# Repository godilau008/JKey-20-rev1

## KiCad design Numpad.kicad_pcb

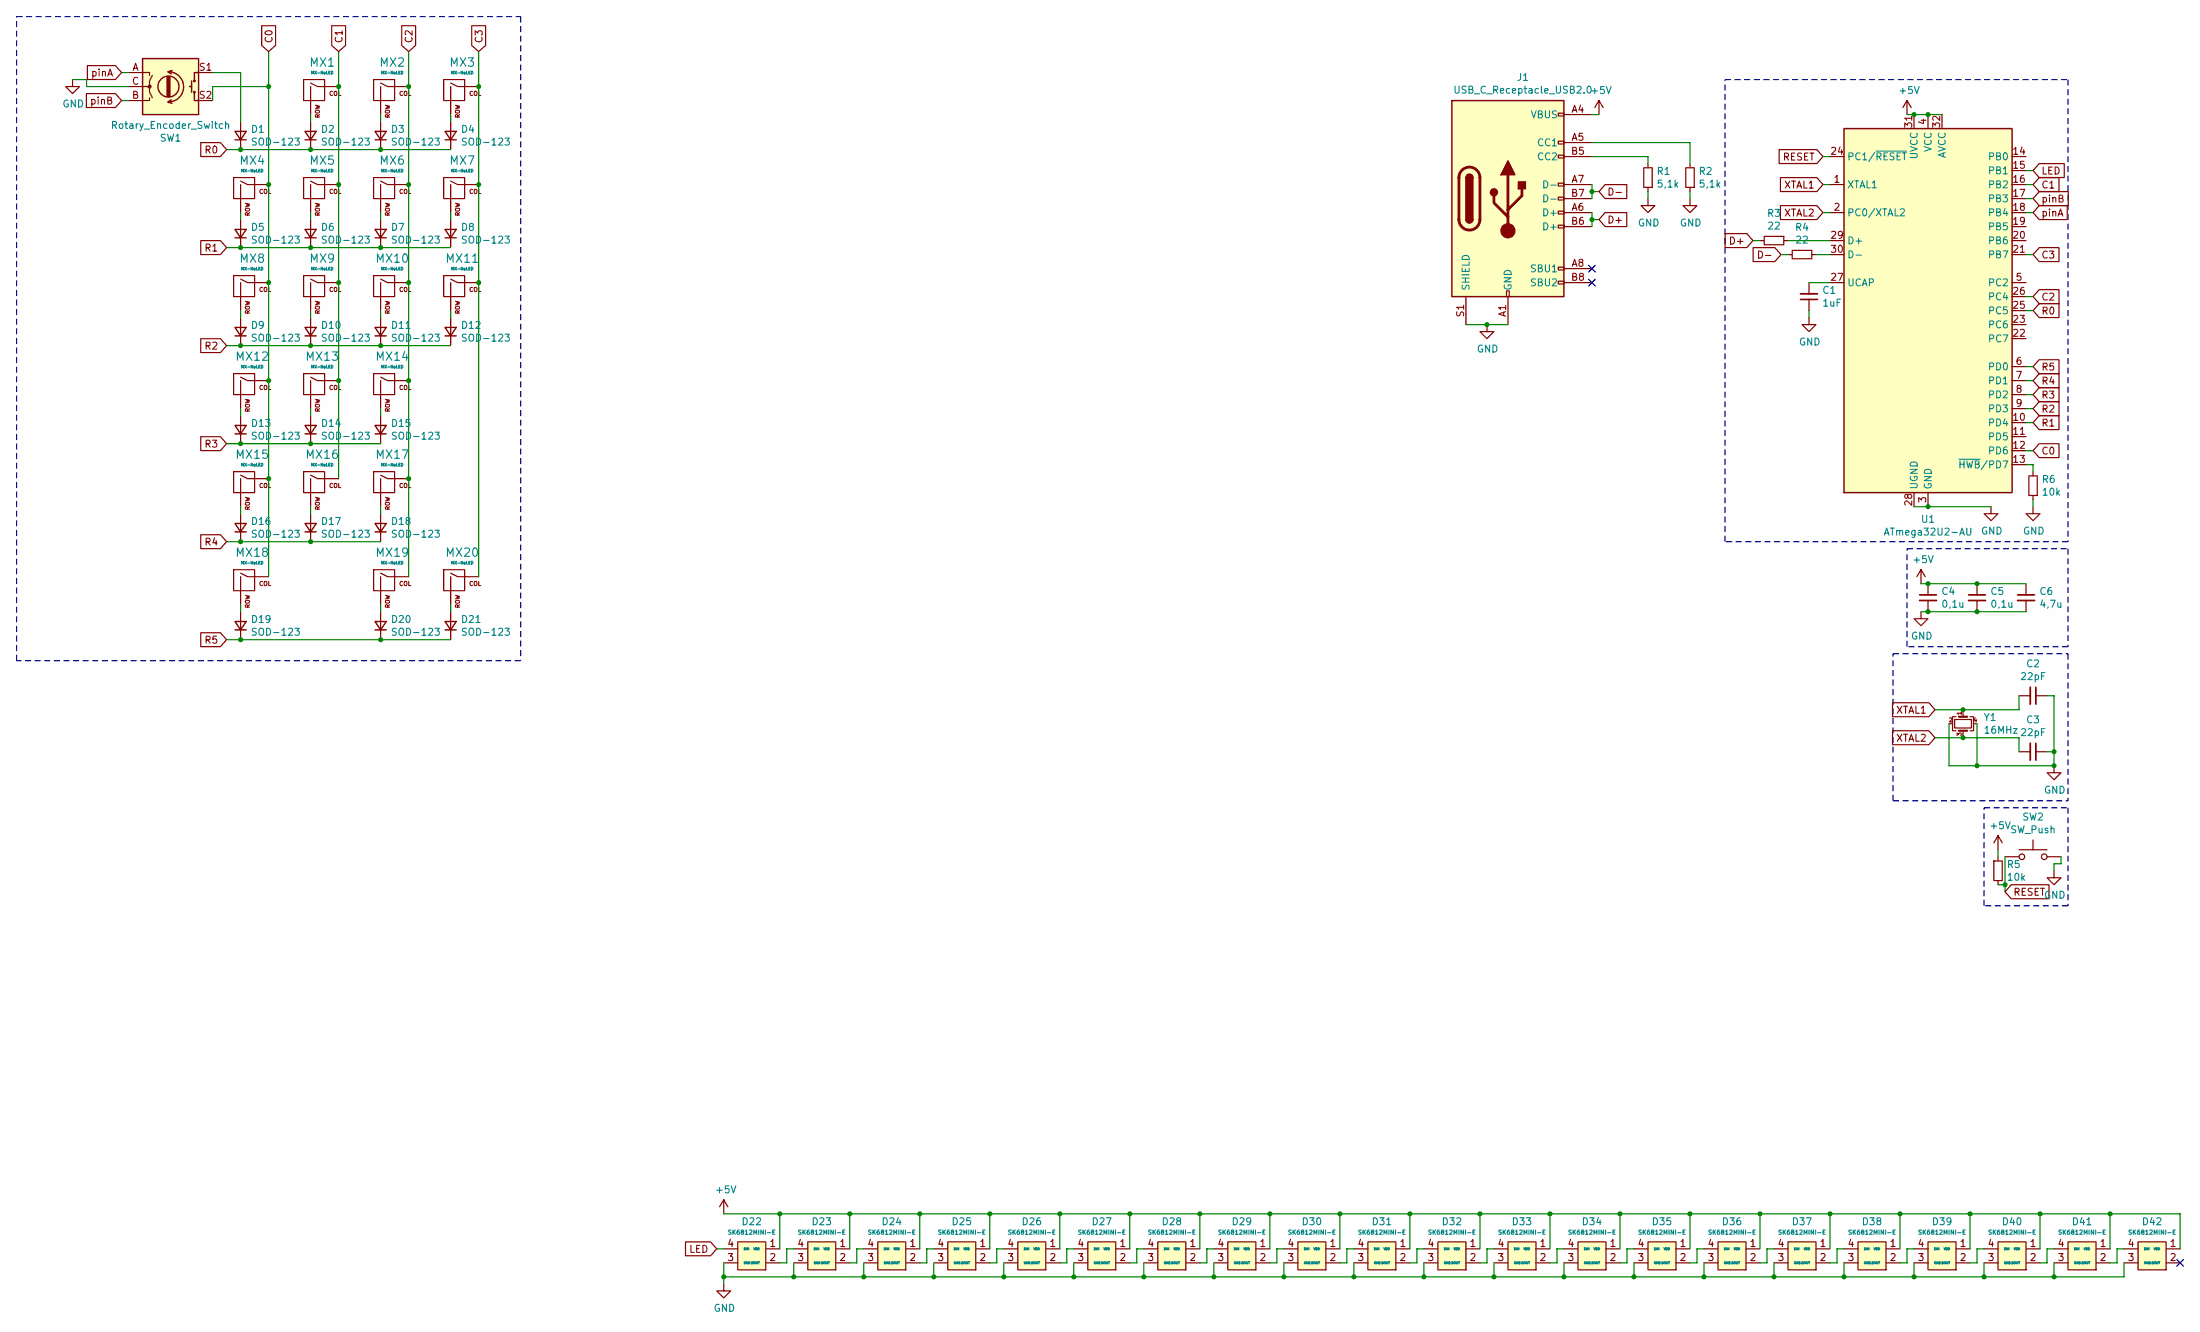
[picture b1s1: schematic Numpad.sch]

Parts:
C1: 1uF; C_0805_2012Metric_Pad1.15x1.40mm_HandSolder
C2, C3: 22pF; C_0805_2012Metric_Pad1.15x1.40mm_HandSolder
C4, C5: 0,1u; C_0805_2012Metric_Pad1.15x1.40mm_HandSolder
C6: 4,7u; C_0805_2012Metric_Pad1.15x1.40mm_HandSolder
D1, D2, D3, D4, D5, D6, D7, D8, D9, D10, D11, D12, D13, D14, D15, D16, D17, D18, D19, D20, D21: SOD-123; D_SOD-123
D22, D23, D24, D25, D26, D27, D28, D29, D30, D31, D32, D33, D34, D35, D36, D37, D38, D39, D40, D41, D42: SK6812MINI-E; LED_SK6812MINI-E_HOLE
J1: USB_C_Receptacle_USB2.0; USB_C_Receptacle_GCT_USB4085
MX1, MX2, MX3, MX4, MX5, MX6, MX7, MX8, MX9, MX10, MX12, MX13, MX14, MX15, MX16, MX17, MX19: MX-NoLED; MXOnly-1U-NoLED
MX11, MX20: MX-NoLED; MXOnly-2U-NoLED-Vertical
MX18: MX-NoLED; MXOnly-2U-NoLED
R1, R2: 5,1k; R_0805_2012Metric_Pad1.15x1.40mm_HandSolder
R3, R4: 22; R_0805_2012Metric_Pad1.15x1.40mm_HandSolder
R5, R6: 10k; R_0805_2012Metric_Pad1.15x1.40mm_HandSolder
SW1: Rotary_Encoder_Switch; RotaryEncoder_Alps_EC11E-Switch_Vertical_H20mm
SW2: SW_Push; SW_SPST_TL3342
U1: ATmega32U2-AU; TQFP-32_7x7mm_P0.8mm
Y1: 16MHz; Crystal_SMD_3225-4Pin_3.2x2.5mm_HandSoldering

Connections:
+5V: C4.1, C5.1, C6.1, D22.1 (VDD), D23.1 (VDD), D24.1 (VDD), D25.1 (VDD), D26.1 (VDD), D27.1 (VDD), D28.1 (VDD), D29.1 (VDD), D30.1 (VDD), D31.1 (VDD), D32.1 (VDD), D33.1 (VDD), D34.1 (VDD), D35.1 (VDD), D36.1 (VDD), D37.1 (VDD), D38.1 (VDD), D39.1 (VDD), D40.1 (VDD), D41.1 (VDD), D42.1 (VDD), J1.A4 (VBUS), J1.A9 (VBUS), J1.B4 (VBUS), J1.B9 (VBUS), R5.1, U1.4 (VCC), U1.31 (UVCC), U1.32 (AVCC)
C0: MX4.1 (COL), MX8.1 (COL), MX12.1 (COL), MX15.1 (COL), MX18.1 (COL), SW1.S2, U1.12 (PD6)
C1: MX1.1 (COL), MX5.1 (COL), MX9.1 (COL), MX13.1 (COL), MX16.1 (COL), U1.16 (PB2)
C2: MX2.1 (COL), MX6.1 (COL), MX10.1 (COL), MX14.1 (COL), MX17.1 (COL), MX19.1 (COL), U1.26 (PC4)
C3: MX3.1 (COL), MX7.1 (COL), MX11.1 (COL), MX20.1 (COL), U1.21 (PB7)
D+: J1.A6 (D+), J1.B6 (D+), R3.2
D-: J1.A7 (D-), J1.B7 (D-), R4.2
GND: C1.1, C2.1, C3.1, C4.2, C5.2, C6.2, D22.3 (GND), D23.3 (GND), D24.3 (GND), D25.3 (GND), D26.3 (GND), D27.3 (GND), D28.3 (GND), D29.3 (GND), D30.3 (GND), D31.3 (GND), D32.3 (GND), D33.3 (GND), D34.3 (GND), D35.3 (GND), D36.3 (GND), D37.3 (GND), D38.3 (GND), D39.3 (GND), D40.3 (GND), D41.3 (GND), D42.3 (GND), J1.A1 (GND), J1.A12 (GND), J1.B1 (GND), J1.B12 (GND), J1.S1 (SHIELD), R1.1, R2.1, R6.1, SW1.C, SW2.2, U1.3 (GND), U1.28 (UGND), Y1.2, Y1.4
LED: D22.4 (DIN), U1.15 (PB1)
unnamed: C1.2, U1.27 (UCAP)
unnamed: D1.2 (A), SW1.S1
unnamed: D2.2 (A), MX1.2 (ROW)
unnamed: D3.2 (A), MX2.2 (ROW)
unnamed: D4.2 (A), MX3.2 (ROW)
unnamed: D5.2 (A), MX4.2 (ROW)
unnamed: D6.2 (A), MX5.2 (ROW)
unnamed: D7.2 (A), MX6.2 (ROW)
unnamed: D8.2 (A), MX7.2 (ROW)
unnamed: D9.2 (A), MX8.2 (ROW)
unnamed: D10.2 (A), MX9.2 (ROW)
unnamed: D11.2 (A), MX10.2 (ROW)
unnamed: D12.2 (A), MX11.2 (ROW)
unnamed: D13.2 (A), MX12.2 (ROW)
unnamed: D14.2 (A), MX13.2 (ROW)
unnamed: D15.2 (A), MX14.2 (ROW)
unnamed: D16.2 (A), MX15.2 (ROW)
unnamed: D17.2 (A), MX16.2 (ROW)
unnamed: D18.2 (A), MX17.2 (ROW)
unnamed: D19.2 (A), MX18.2 (ROW)
unnamed: D20.2 (A), MX19.2 (ROW)
unnamed: D21.2 (A), MX20.2 (ROW)
unnamed: D22.2 (DOUT), D23.4 (DIN)
unnamed: D23.2 (DOUT), D24.4 (DIN)
unnamed: D24.2 (DOUT), D25.4 (DIN)
unnamed: D25.2 (DOUT), D26.4 (DIN)
unnamed: D26.2 (DOUT), D27.4 (DIN)
unnamed: D27.2 (DOUT), D28.4 (DIN)
unnamed: D28.2 (DOUT), D29.4 (DIN)
unnamed: D29.2 (DOUT), D30.4 (DIN)
unnamed: D30.2 (DOUT), D31.4 (DIN)
unnamed: D31.2 (DOUT), D32.4 (DIN)
unnamed: D32.2 (DOUT), D33.4 (DIN)
unnamed: D33.2 (DOUT), D34.4 (DIN)
unnamed: D34.2 (DOUT), D35.4 (DIN)
unnamed: D35.2 (DOUT), D36.4 (DIN)
unnamed: D36.2 (DOUT), D37.4 (DIN)
unnamed: D37.2 (DOUT), D38.4 (DIN)
unnamed: D38.2 (DOUT), D39.4 (DIN)
unnamed: D39.2 (DOUT), D40.4 (DIN)
unnamed: D40.2 (DOUT), D41.4 (DIN)
unnamed: D41.2 (DOUT), D42.4 (DIN)
unnamed: J1.A5 (CC1), R2.2
unnamed: J1.B5 (CC2), R1.2
unnamed: R3.1, U1.29 (D+)
unnamed: R4.1, U1.30 (D-)
unnamed: R6.2, U1.13 (~HWB~/PD7)
R0: D1.1 (K), D2.1 (K), D3.1 (K), D4.1 (K), U1.25 (PC5)
R1: D5.1 (K), D6.1 (K), D7.1 (K), D8.1 (K), U1.10 (PD4)
R2: D9.1 (K), D10.1 (K), D11.1 (K), D12.1 (K), U1.9 (PD3)
R3: D13.1 (K), D14.1 (K), D15.1 (K), U1.8 (PD2)
R4: D16.1 (K), D17.1 (K), D18.1 (K), U1.7 (PD1)
R5: D19.1 (K), D20.1 (K), D21.1 (K), U1.6 (PD0)
RESET: R5.2, SW2.1, U1.24 (PC1/~RESET)
XTAL1: C2.2, U1.1 (XTAL1), Y1.1
XTAL2: C3.2, U1.2 (PC0/XTAL2), Y1.3
pinA: SW1.A, U1.18 (PB4)
pinB: SW1.B, U1.17 (PB3)

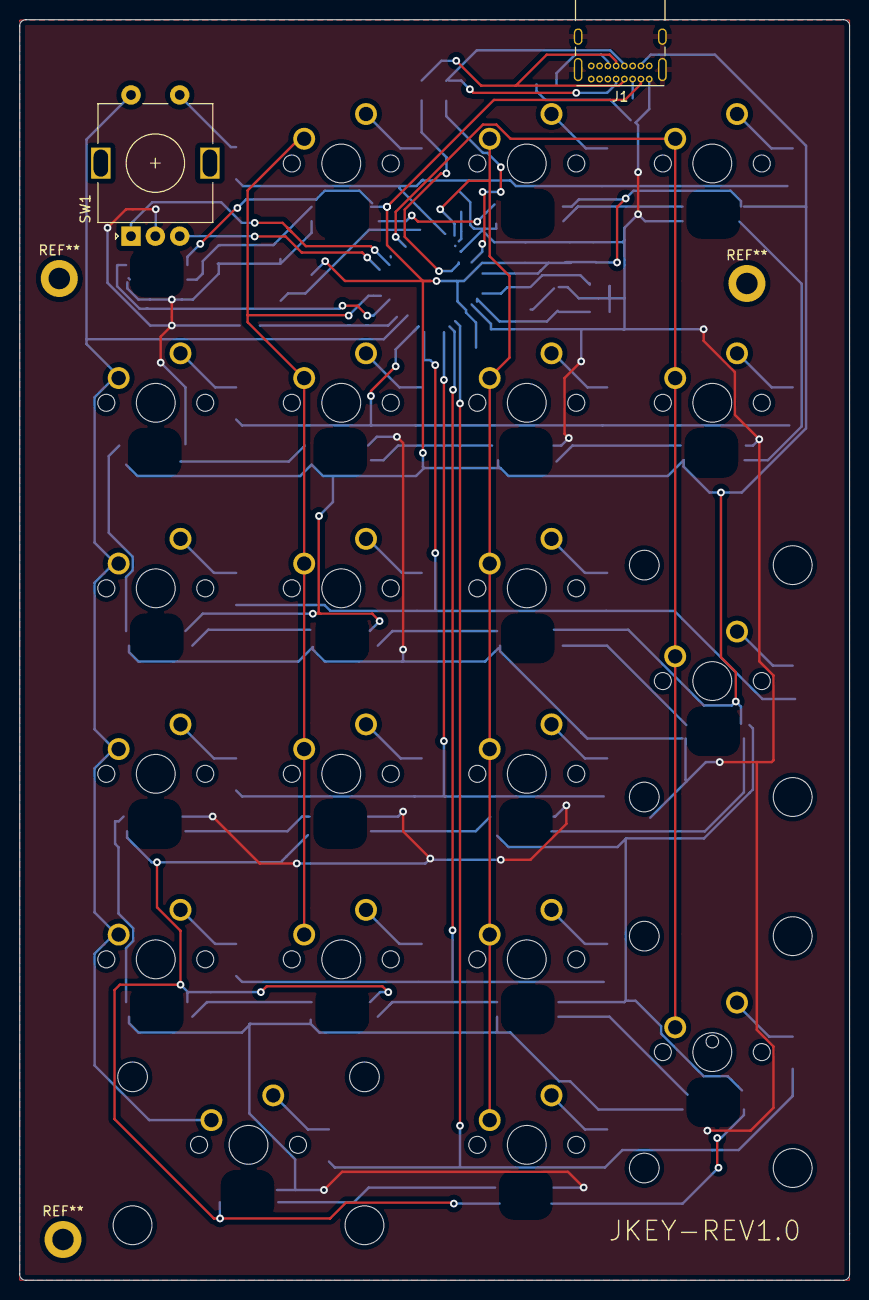
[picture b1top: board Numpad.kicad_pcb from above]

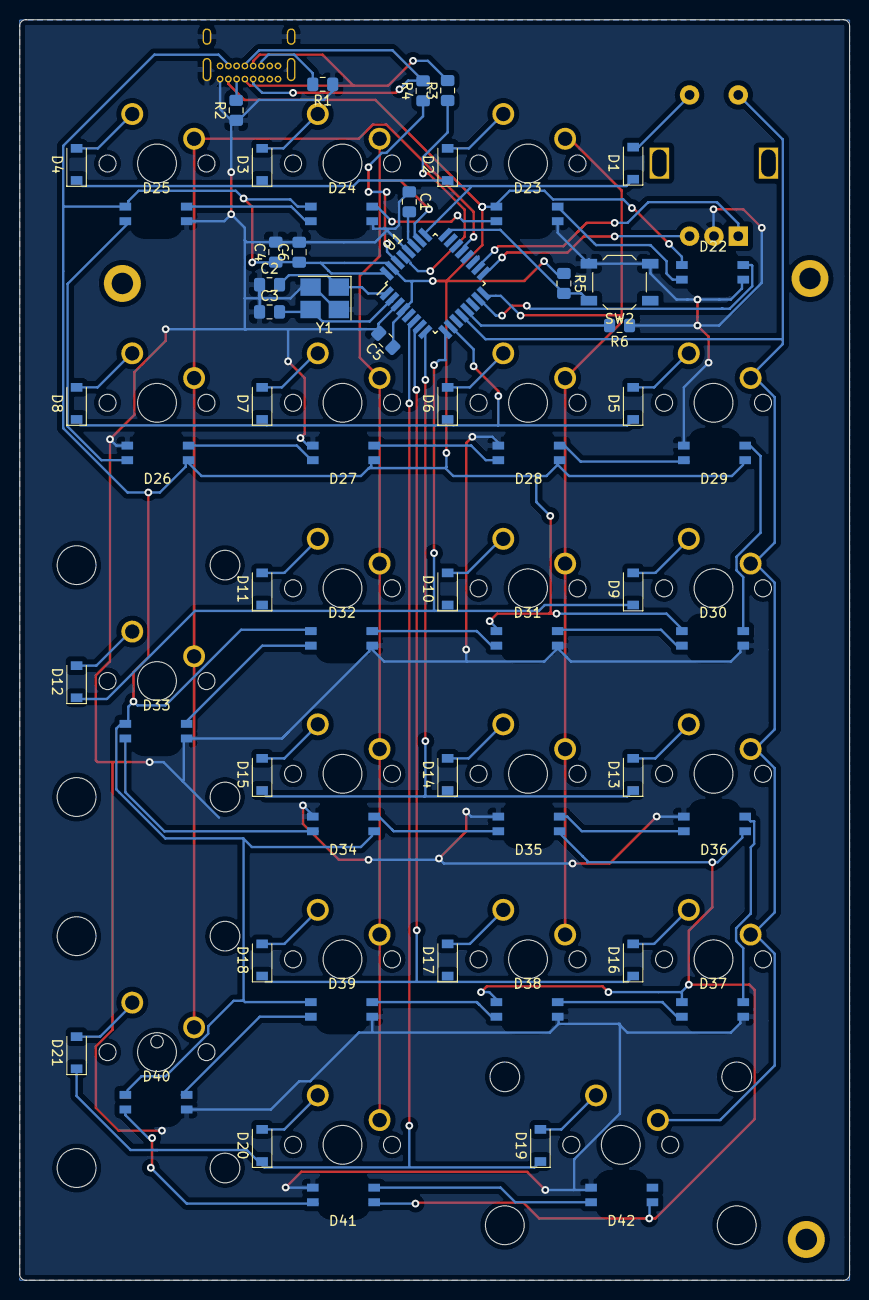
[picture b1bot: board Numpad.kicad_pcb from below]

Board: 2 copper layers, 85.2 x 129.4 mm, 79 parts (57 on the bottom side), 67 nets.
